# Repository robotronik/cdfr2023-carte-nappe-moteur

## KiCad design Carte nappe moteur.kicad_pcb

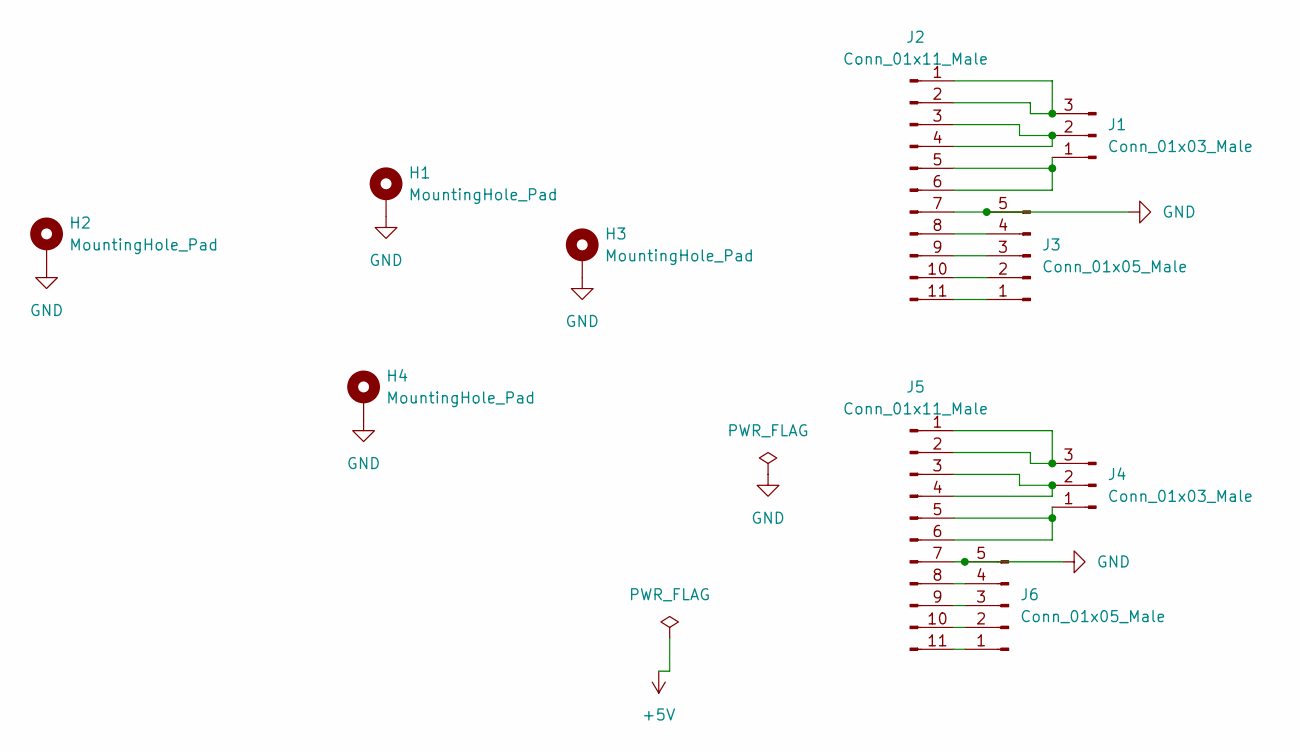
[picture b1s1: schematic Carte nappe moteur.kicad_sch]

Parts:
H1, H2, H3, H4: MountingHole_Pad; MountingHole_3.2mm_M3_Pad_Via
J1, J4: Conn_01x03_Male; CUI_TBP02R1-381-03BE
J2, J5: Conn_01x11_Male; Molex-52610-1133
J3, J6: Conn_01x05_Male; CUI_TBP02R1-381-05BE

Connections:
GND: H1.1, H2.1, H3.1, H4.1, J2.7, J3.5, J5.7, J6.5; also elsewhere on the board
unnamed: J1.1, J2.5, J2.6
unnamed: J1.2, J2.3, J2.4
unnamed: J1.3, J2.1, J2.2
unnamed: J2.8, J3.4
unnamed: J2.9, J3.3
unnamed: J2.10, J3.2
unnamed: J2.11, J3.1
unnamed: J4.1, J5.5, J5.6
unnamed: J4.2, J5.3, J5.4
unnamed: J4.3, J5.1, J5.2
unnamed: J5.8, J6.4
unnamed: J5.9, J6.3
unnamed: J5.10, J6.2
unnamed: J5.11, J6.1

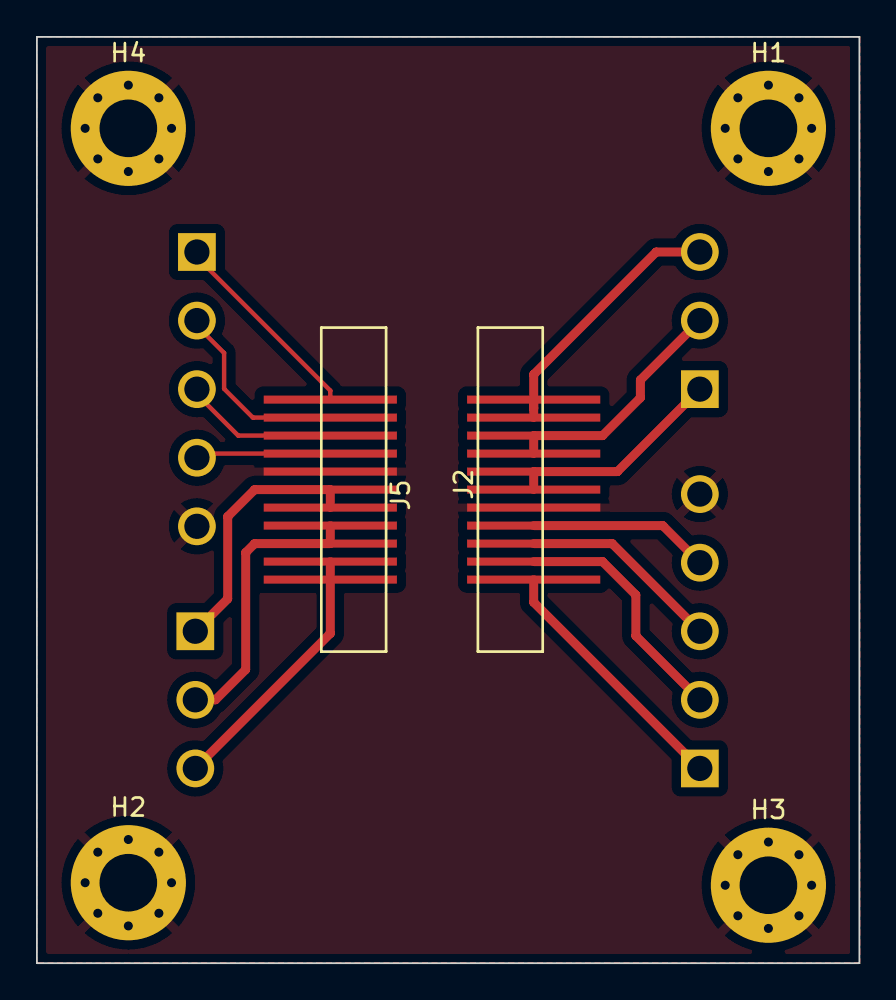
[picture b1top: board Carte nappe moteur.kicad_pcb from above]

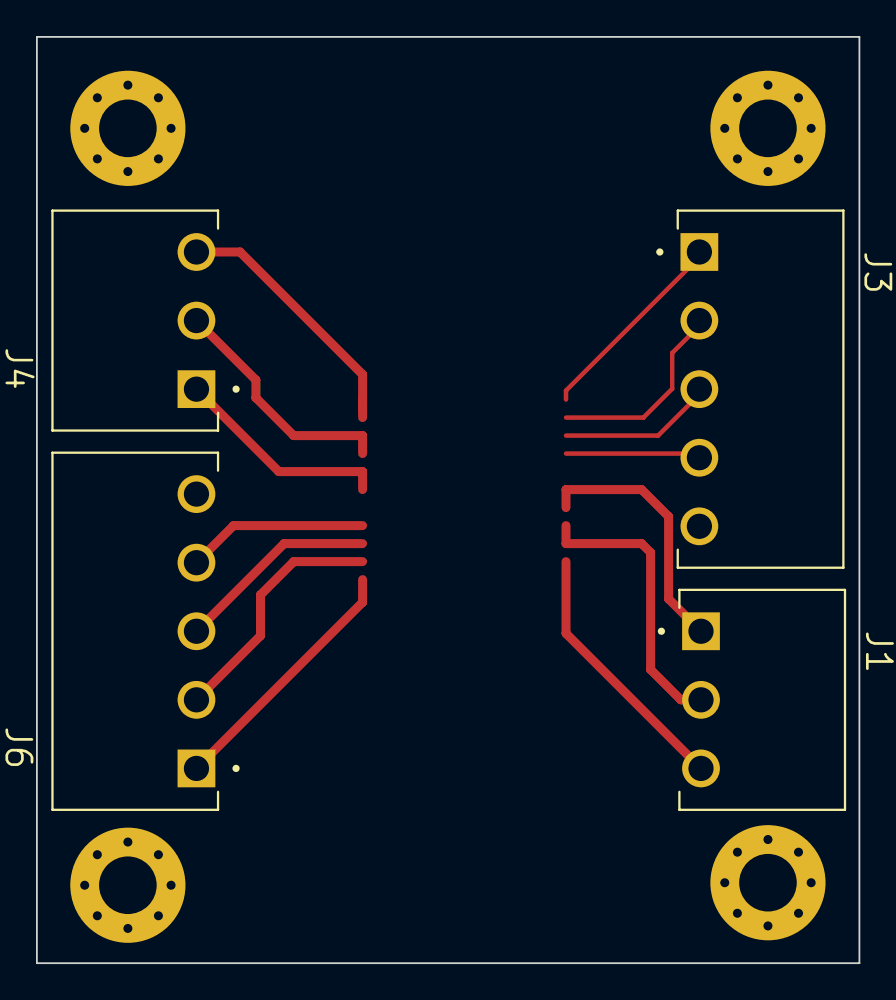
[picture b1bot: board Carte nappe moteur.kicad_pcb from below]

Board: 2 copper layers, 45.7 x 51.5 mm, 10 parts (4 on the bottom side), 15 nets.

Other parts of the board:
H?: MountingHole_Pad; MountingHole_3.2mm_M3_Pad_Via

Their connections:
GND: H?.1; also elsewhere on the board

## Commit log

2023-01-19 Reduction de la carte pcb
2023-01-22 Fix overlap pieces
2023-02-08 Résolution problème de symétrie
2023-02-08 gitigore
